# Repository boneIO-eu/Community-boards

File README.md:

# BoneIO Community Boards

This repository contains boards made by boneIO community members. Everybody can share their work, which allows your work to be tested by community!

Requirements:

- Each board need to be in separate directory.
- In directory you need to create files:
  - AUTHORS.md which template you can copy from main directory. It has to constist authors of the board.
  - README.md - description of the board, what is purpose of the board, what it can do, how to connect it etc. 3D visualisation in the file is very welcome.

You want to create board for community!
This is the right place!

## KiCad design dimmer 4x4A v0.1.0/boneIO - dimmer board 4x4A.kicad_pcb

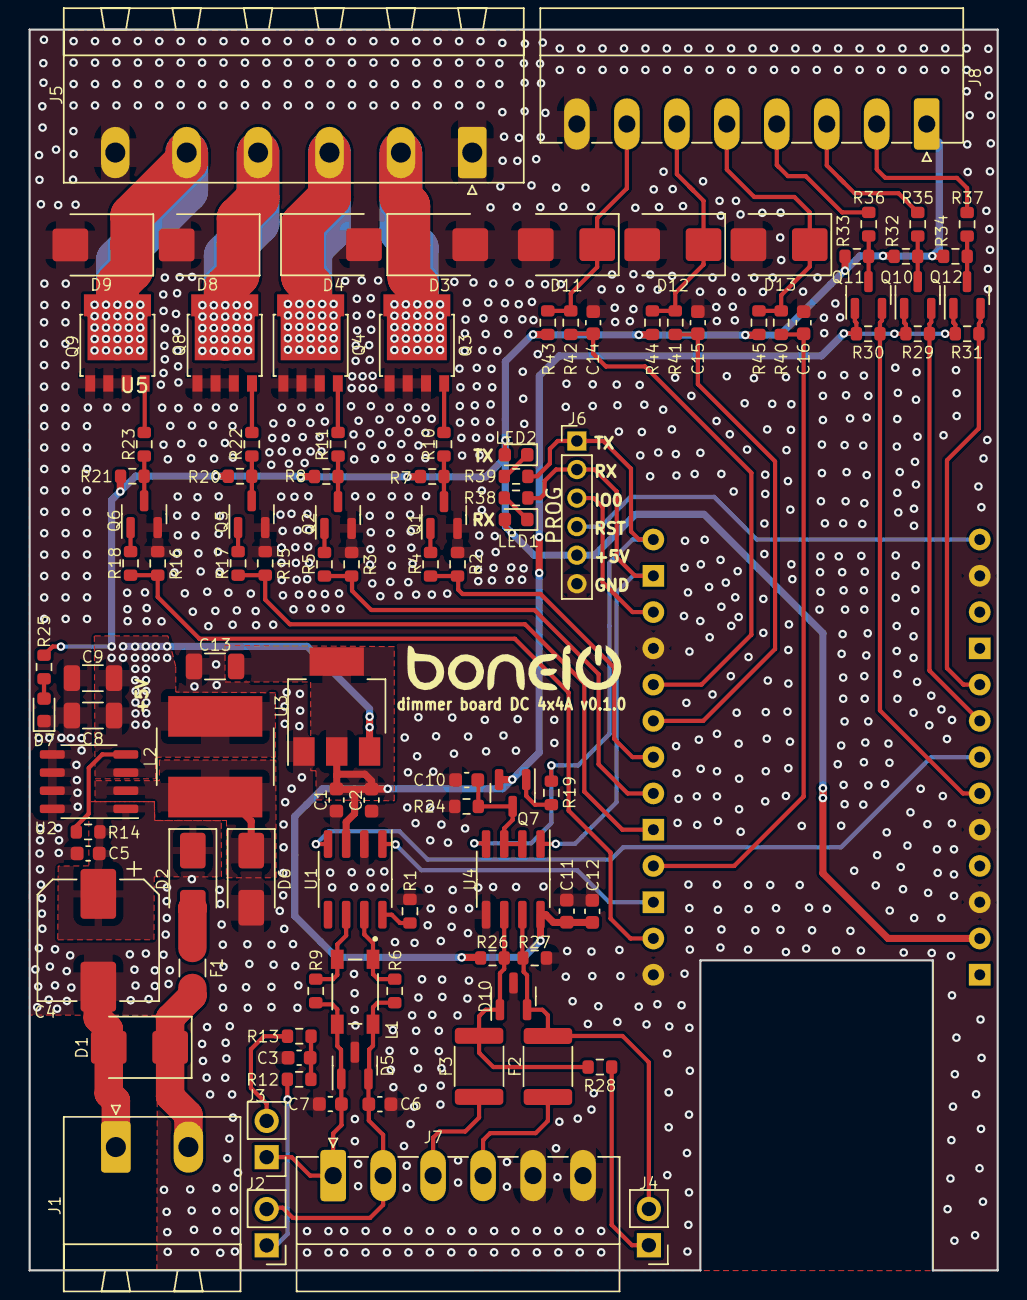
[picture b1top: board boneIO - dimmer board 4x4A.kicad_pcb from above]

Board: 2 copper layers, 67.8 x 86.9 mm, 106 parts (0 on the bottom side), 67 nets.

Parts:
C1, C11: 10uF/C0805; C_0603_1608Metric
C2, C12, C14, C15, C16: 100nF/C0603; C_0603_1608Metric
C3: 4.7nF/C0603; C_0603_1608Metric
C4: 100uF/50V; CP_Elec_8x10
C5, C10: 100n; C_0603_1608Metric
C6, C7: 47pF/C0603; C_0603_1608Metric
C8, C9, C13: 10uF; C_1206_3216Metric
D1, D3, D4, D8, D9: SMBJ28CA; D_SMB
D2, D6: SS34; D_SMA
D5: PESD1CAN; SOT-23
D7: LED_RED; LED_0603_1608Metric
D10: SM712_SOT23; SOT-23
D11, D12, D13: P6SMB6.8A; D_SMB
F1: BSMD1206-100-24V; Fuse_1206_3216Metric
F2, F3: JK-mSMD010-60; Fuse_1812_4532Metric
J1: Screw_Terminal_01x02; PhoenixContact_MSTBA_2,5_2-G-5,08_1x02_P5.08mm_Horizontal
J2, J3: Jumper 60.4R; PinHeader_1x02_P2.54mm_Vertical
J4: Jumper 120R; PinHeader_1x02_P2.54mm_Vertical
J5: RGBW; PhoenixContact_MSTBA_2,5_6-G_1x06_P5.00mm_Horizontal
J6: PROG; PinHeader_1x06_P2.00mm_Vertical
J7: CAN&RS; PhoenixContact_MC_1,5_6-G-3.5_1x06_P3.50mm_Horizontal
J8: Screw_Terminal_01x08; PhoenixContact_MC_1,5_8-G-3.5_1x08_P3.50mm_Horizontal
L1: ACT45B-510; FIL_ACT45B-510-2P-TL003
L2: 68uH; L_Bourns_SRN8040TA
LED1, LED2: LED_BLUE/L0603; LED_0603_1608Metric
Q1, Q2, Q5, Q6: BC817; SOT-23
Q3, Q4, Q8, Q9: PSMN1R2-30YLC; LFPAK56
Q7: BC807; SOT-23
Q10, Q11, Q12: BSS138; SOT-23
R1, R2, R3, R7, R8, R15, R16, R20, R21, R29, R30, R31, R32, R33, R34, R43, R44, R45: 10k/R0603; R_0603_1608Metric
R4, R5, R10, R11, R17, R18, R22, R23: 4.7k/R0603; R_0603_1608Metric
R6, R9: 0k/R0603; R_0603_1608Metric
R12: 60.4k/R0603; R_0603_1608Metric
R13: 60.4R/R0603; R_0603_1608Metric
R14: 100k; R_0603_1608Metric
R19, R24, R26, R27: 4.7k; R_0603_1608Metric
R25, R38, R39: 1.2k/R0603; R_0603_1608Metric
R28: 120R; R_0603_1608Metric
R35, R36, R37: 330R/R0603; R_0603_1608Metric
R40, R41, R42: 330R; R_0603_1608Metric
U1: SN65HVD230; SOIC-8_3.9x4.9mm_P1.27mm
U2: 5V; SO-8_3.9x4.9mm_P1.27mm
U3: AMS1117-3.3; SOT-223-3_TabPin2
U4: MAX485E; SOIC-8_3.9x4.9mm_P1.27mm
U5: WT32-ETH01; WT32-ETH

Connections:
+3V3: C1.2, C2.2, C11.2, C12.2, C13.1, Q7.2 (E), Q10.1 (G), Q11.1 (G), Q12.1 (G), R26.1, R29.1, R30.1, R31.1, U1.3 (VCC), U3.2 (VO), U4.8 (VCC)
+5V: C8.1, C9.1, J6.5, J8.1, L2.2, LED1.2 (A), LED2.2 (A), R7.1, R8.1, R20.1, R21.1, R25.1, R32.1, R33.1, R34.1, R43.1, R44.2, R45.2, U2.3 (FB), U3.3 (VI), U5.25 (5V)
+24V: C4.1, C5.1, D2.1 (K), R14.1, U2.1 (VIN)
A+_OUT: F3.2, J7.3
B-_OUT: F2.2, J7.4
BLUE_OUT: D8.1 (A1), J5.4, Q8.5 (D)
CAN_H: C6.2, D5.2, J2.2, J7.2, L1.4, R6.1
CAN_L: C7.1, D5.1, J3.1, J7.1, L1.3, R9.2
ESP_EN: J6.4, U5.14 (EN)
GND: C1.1, C2.1, C3.2, C4.2, C5.2, C6.1, C7.2, C8.2, C9.2, C10.2, C11.1, C12.1, C13.2, C14.2, C15.2, C16.2, D1.2 (A2), D3.2 (A2), D4.2 (A2), D5.3, D6.2 (A), D7.1 (K), D8.2 (A2), D9.2 (A2), D10.3 (common), D11.2 (A), D12.2 (A), D13.2 (A), J1.1, J5.1, J5.6, J6.6, J7.5, J7.6, J8.8, Q1.2 (E), Q2.2 (E), Q3.1 (S), Q3.2 (S), Q3.3 (S), Q4.1 (S), Q4.2 (S), Q4.3 (S), Q5.2 (E), Q6.2 (E), Q8.1 (S), Q8.2 (S), Q8.3 (S), Q9.1 (S), Q9.2 (S), Q9.3 (S), R1.2, R2.2, R3.2, R15.2, R16.2, R24.2, R27.2, U1.2 (GND), U2.5 (GND), U2.6 (GND), U2.7 (GND), U2.8 (GND), U3.1 (GND), U4.5 (GND), U5.4 (GND), U5.13 (GND), U5.15 (GND), U5.22 (GND), U5.24 (GND)
GPIO0: J6.3, U5.3 (IO0)
GREEN_OUT: D4.1 (A1), J5.3, Q4.5 (D)
INPUT_1: C14.1, R42.1, U5.5 (IO39)
INPUT_2: C15.1, R41.1, U5.6 (IO36)
INPUT_3: C16.1, R40.1, U5.10 (IO35)
unnamed: C3.1, R12.1, R13.2
unnamed: D2.2 (A), F1.1
unnamed: D6.1 (K), L2.1, U2.2 (OUT)
unnamed: D7.2 (A), R25.2
unnamed: D10.1 (A1), F3.1, R26.2, R28.2, U4.6 (A)
unnamed: D10.2 (A2), F2.1, J4.2, R27.1, U4.7 (B)
unnamed: D11.1 (K), J8.7, R42.2, R43.2
unnamed: D12.1 (K), J8.6, R41.2, R44.1
unnamed: D13.1 (K), J8.5, R40.2, R45.1
unnamed: J2.1, R12.2
unnamed: J3.2, R13.1
unnamed: J4.1, R28.1
unnamed: LED1.1 (K), R38.2
unnamed: LED2.1 (K), R39.2
unnamed: Q1.1 (B), R4.1
unnamed: Q1.3 (C), R7.2, R10.2
unnamed: Q2.1 (B), R5.1
unnamed: Q2.3 (C), R8.2, R11.2
unnamed: Q3.4 (G), R10.1
unnamed: Q4.4 (G), R11.1
unnamed: Q5.1 (B), R17.1
unnamed: Q5.3 (C), R20.2, R22.2
unnamed: Q6.1 (B), R18.1
unnamed: Q6.3 (C), R21.2, R23.2
unnamed: Q7.1 (B), R19.1
unnamed: C10.1, Q7.3 (C), R24.1, U4.2 (~RE), U4.3 (DE)
unnamed: Q8.4 (G), R22.1
unnamed: Q9.4 (G), R23.1
unnamed: Q10.3 (D), R32.2, R35.2
unnamed: Q11.3 (D), R33.2, R36.2
unnamed: Q12.3 (D), R34.2, R37.2
unnamed: L1.1, R6.2, U1.7 (CANH)
unnamed: L1.2, R9.1, U1.6 (CANL)
unnamed: R1.1, U1.8 (Rs)
unnamed: R14.2, U2.4 (ON/OFF)
OUT_1: R2.1, R4.2, U5.7 (IO15)
OUT_2: R3.1, R5.2, U5.8 (IO14)
OUT_3: R15.1, R17.2, U5.9 (IO12)
OUT_4: R16.1, R18.2, U5.12 (IO2)
RED_OUT: D3.1 (A1), J5.2, Q3.5 (D)
RX: J6.2, R38.1, U4.1 (RO), U5.2 (RXD)
RX_CAN: U1.4 (R), U5.20 (IO5)
TX: J6.1, R19.2, R39.1, U4.4 (DI), U5.1 (TXD)
TX_CAN: U1.1 (D), U5.11 (IO4)
VDD: D1.1 (A1), F1.2, J1.2
WHITE_OUT: D9.1 (A1), J5.5, Q9.5 (D)
WS281x1: Q12.2 (S), R31.2, U5.18 (IO32)
WS281x1_OUT: J8.2, R37.1
WS281x2: Q10.2 (S), R29.2, U5.19 (IO33)
WS281x2_OUT: J8.3, R35.1
WS281x3: Q11.2 (S), R30.2, U5.21 (IO17)
WS281x3_OUT: J8.4, R36.1

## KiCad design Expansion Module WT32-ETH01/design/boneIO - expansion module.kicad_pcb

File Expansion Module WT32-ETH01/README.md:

# boneIO module expander WT32-ETH01

This software script allows you to use the ESP32 + RS485 transceiver to interact with relay boards to boneIO.

It provides all known information via MQTT.

This allows you to integrate the device with Home Assistant.

You can find the configuration YAML files in the `yaml` folder.

## Foto

## Pinout
1. 
Power input
24 DC power supply

2.
RS485
TX 				- GPIO1
RX 				- GPIO3
Flow Control  	- GPIO4

3. 
USB
USB-C is for uploading software

4.
WT32-ETH01
ESP32 controller right with Ethernet for MQTT communication

5.
INPUTS
Digital inputs controlled by low state
IN1 - GPIO39
IN2 - GPIO36
IN3 - GPIO15
IN4 - GPIO14
IN5 - GPIO35
IN6 - GPIO17

6.
I2C
SDA - GPIO32
SCL - GPIO33
Frequency - 100kHz

7.
1-WIRE
DATA - GPIO5

Exit and input description:

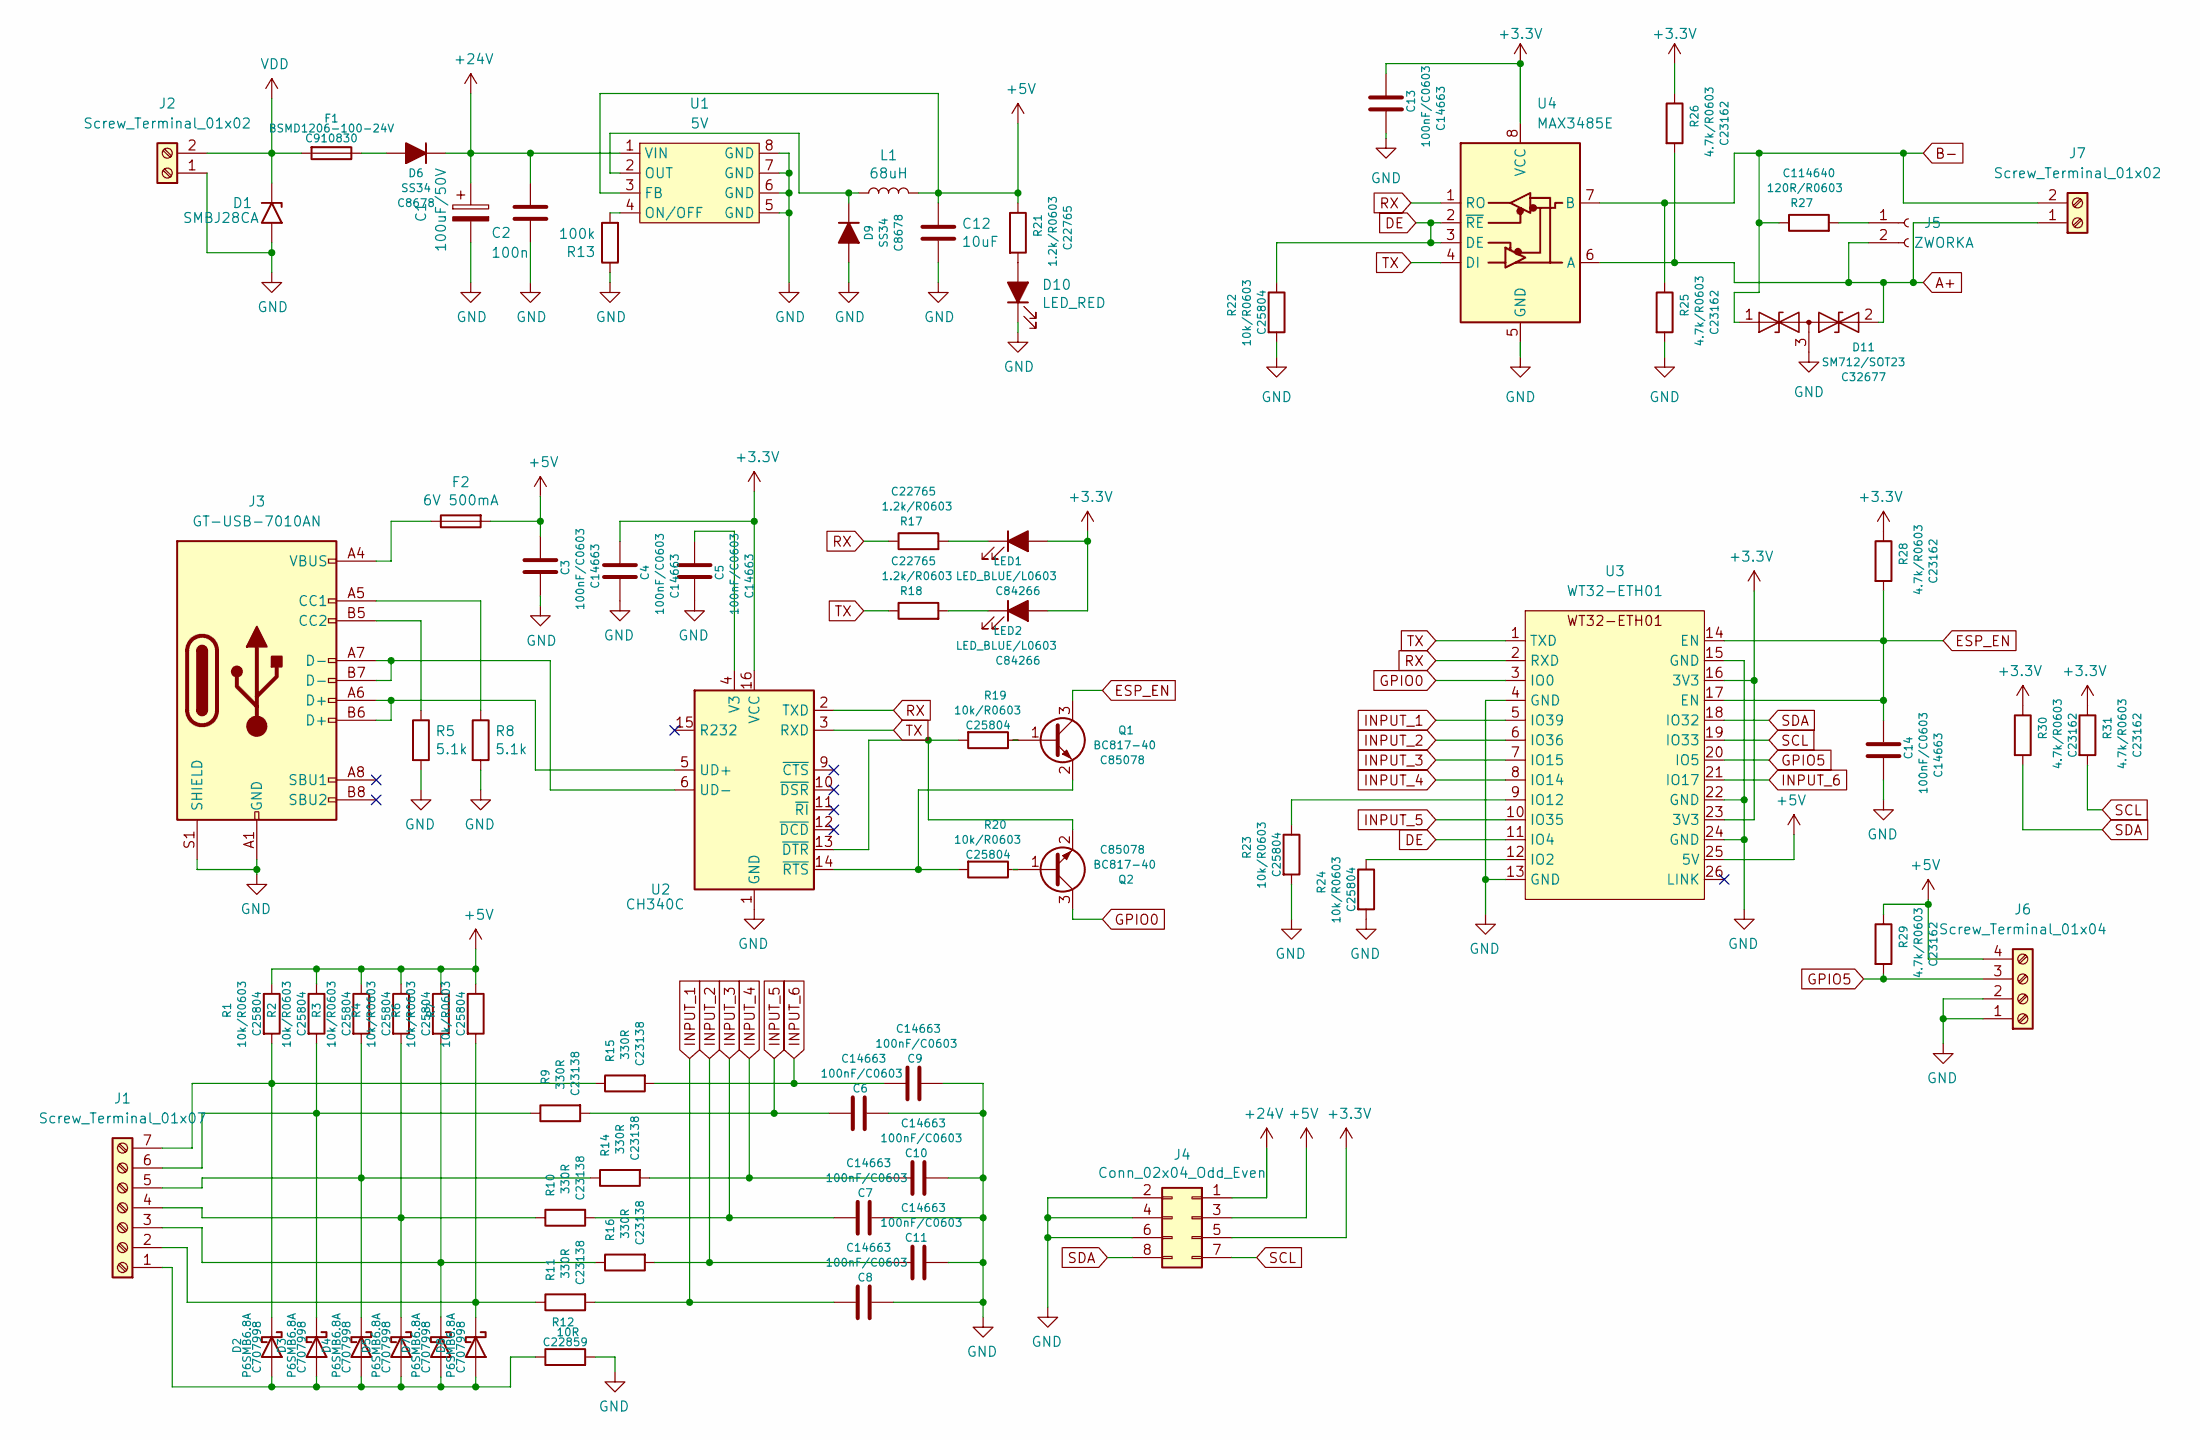
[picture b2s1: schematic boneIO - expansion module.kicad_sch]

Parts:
C1: 100uF/50V; CP_Elec_8x10; JLCPCB C72480
C2: 100n; C_0603_1608Metric; JLCPCB C14663
C3, C4, C5, C6, C7, C8, C9, C10, C11, C13, C14: 100nF/C0603; C_0603_1608Metric; JLCPCB C14663
C12: 10uF; C_1206_3216Metric; JLCPCB C107149
D1: SMBJ28CA; D_SMB
D2, D3, D4, D5, D7, D8: P6SMB6.8A; D_SMB; JLCPCB C707998
D6, D9: SS34; D_SMA; JLCPCB C8678
D10: LED_RED; LED_0603_1608Metric; JLCPCB C84256
D11: SM712/SOT23; SOT-23; JLCPCB C32677
F1: BSMD1206-100-24V; Fuse_1206_3216Metric; JLCPCB C910830
F2: 6V 500mA; Fuse_1206_3216Metric
J1: Screw_Terminal_01x07; PhoenixContact_MSTBA_2,5_7-G-5,08_1x07_P5.08mm_Horizontal
J2, J7: Screw_Terminal_01x02; PhoenixContact_MSTBA_2,5_2-G-5,08_1x02_P5.08mm_Horizontal
J3: GT-USB-7010AN; USB_C_Receptacle_HRO_TYPE-C-31-M-12
J4: Conn_02x04_Odd_Even; PinHeader_2x04_P2.54mm_Vertical
J5: ZWORKA; PinHeader_1x02_P2.54mm_Vertical
J6: Screw_Terminal_01x04; PhoenixContact_MSTBA_2,5_4-G-5,08_1x04_P5.08mm_Horizontal
L1: 68uH; L_Bourns_SRN8040TA; JLCPCB C338848
LED1, LED2: LED_BLUE/L0603; LED_0603_1608Metric; JLCPCB C84266
Q1, Q2: BC817-40; SOT-23; JLCPCB C85078
R1, R2, R3, R4, R6, R7, R19, R20, R22, R23, R24: 10k/R0603; R_0603_1608Metric; JLCPCB C25804
R5, R8: 5.1k; R_0603_1608Metric
R9, R10, R11, R14, R15, R16: 330R; R_0603_1608Metric; JLCPCB C23138
R12: 10R; R_0603_1608Metric; JLCPCB C22859
R13: 100k; R_0603_1608Metric; JLCPCB C269704
R17, R18, R21: 1.2k/R0603; R_0603_1608Metric; JLCPCB C22765
R25, R26, R28, R29, R30, R31: 4.7k/R0603; R_0603_1608Metric; JLCPCB C23162
R27: 120R/R0603; R_0603_1608Metric; JLCPCB C114640
U1: 5V; SO-8_3.9x4.9mm_P1.27mm
U2: CH340C; SOIC-16_3.9x9.9mm_P1.27mm
U3: WT32-ETH01; WT32_ETH01
U4: MAX3485E; SOP-8_3.9x4.9mm_P1.27mm; JLCPCB C9943

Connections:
+3V3: C4.1, C13.1, J4.5, LED1.2 (A), LED2.2 (A), R26.1, R28.1, R30.1, R31.1, U2.16 (VCC), U3.16 (3V3), U3.23 (3V3), U4.8 (VCC)
+5V: C3.1, C12.1, F2.2, J4.3, J6.4, L1.2, R1.1, R2.1, R3.1, R4.1, R6.1, R7.1, R21.1, R29.1, U1.3 (FB), U3.25 (5V)
+24V: C1.1, C2.1, D6.1 (K), J4.1, U1.1 (VIN)
A+: D11.2 (A2), J5.2, J7.1, R26.2, U4.6 (A)
B-: D11.1 (A1), J7.2, R25.1, R27.1, U4.7 (B)
DE: R22.1, U3.11 (IO4), U4.2 (~RE), U4.3 (DE)
ESP_EN: C14.1, Q1.3 (C), R28.2, U3.14 (EN), U3.17 (EN)
GND: C1.2, C2.2, C3.2, C4.2, C5.2, C6.2, C7.2, C8.2, C9.2, C10.2, C11.2, C12.2, C13.2, C14.2, D1.2 (A2), D9.2 (A), D10.1 (K), D11.3 (common), J2.1, J3.A1 (GND), J3.A12 (GND), J3.B1 (GND), J3.B12 (GND), J3.S1 (SHIELD), J4.2, J4.4, J4.6, J6.1, J6.2, R5.2, R8.2, R12.2, R13.1, R22.2, R23.2, R24.2, R25.2, U1.5 (GND), U1.6 (GND), U1.7 (GND), U1.8 (GND), U2.1 (GND), U3.4 (GND), U3.13 (GND), U3.15 (GND), U3.22 (GND), U3.24 (GND), U4.5 (GND)
GPIO0: Q2.3 (C), U3.3 (IO0)
GPIO5: J6.3, R29.2, U3.20 (IO5)
INPUT_1: C8.1, R11.2, U3.5 (IO39)
INPUT_2: C11.1, R16.2, U3.6 (IO36)
INPUT_3: C7.1, R10.2, U3.7 (IO15)
INPUT_4: C10.1, R14.2, U3.8 (IO14)
INPUT_5: C6.1, R9.2, U3.10 (IO35)
INPUT_6: C9.1, R15.2, U3.21 (IO17)
unnamed: C5.1, U2.4 (V3)
unnamed: D2.1 (K), J1.7, R1.2, R15.1
unnamed: D2.2 (A), D3.2 (A), D4.2 (A), D5.2 (A), D7.2 (A), D8.2 (A), J1.1, R12.1
unnamed: D3.1 (K), J1.6, R2.2, R9.1
unnamed: D4.1 (K), J1.5, R3.2, R14.1
unnamed: D5.1 (K), J1.4, R4.2, R10.1
unnamed: D6.2 (A), F1.1
unnamed: D7.1 (K), J1.3, R6.2, R16.1
unnamed: D8.1 (K), J1.2, R7.2, R11.1
unnamed: D9.1 (K), L1.1, U1.2 (OUT)
unnamed: D10.2 (A), R21.2
unnamed: F2.1, J3.A4 (VBUS), J3.A9 (VBUS), J3.B4 (VBUS), J3.B9 (VBUS)
unnamed: J3.A5 (CC1), R8.1
unnamed: J3.A6 (D+), J3.B6 (D+), U2.5 (UD+)
unnamed: J3.A7 (D-), J3.B7 (D-), U2.6 (UD-)
unnamed: J3.B5 (CC2), R5.1
unnamed: J5.1, R27.2
unnamed: LED1.1 (K), R17.2
unnamed: LED2.1 (K), R18.2
unnamed: Q1.1 (B), R19.1
unnamed: Q1.2 (E), R20.2, U2.14 (~RTS)
unnamed: Q2.1 (B), R20.1
unnamed: Q2.2 (E), R19.2, U2.13 (~DTR)
unnamed: R13.2, U1.4 (ON/OFF)
unnamed: R23.1, U3.9 (IO12)
unnamed: R24.1, U3.12 (IO2)
RX: R17.1, U2.2 (TXD), U3.2 (RXD), U4.1 (RO)
SCL: J4.7, R31.2, U3.19 (IO33)
SDA: J4.8, R30.2, U3.18 (IO32)
TX: R18.1, U2.3 (RXD), U3.1 (TXD), U4.4 (DI)
VDD: D1.1 (A1), F1.2, J2.2

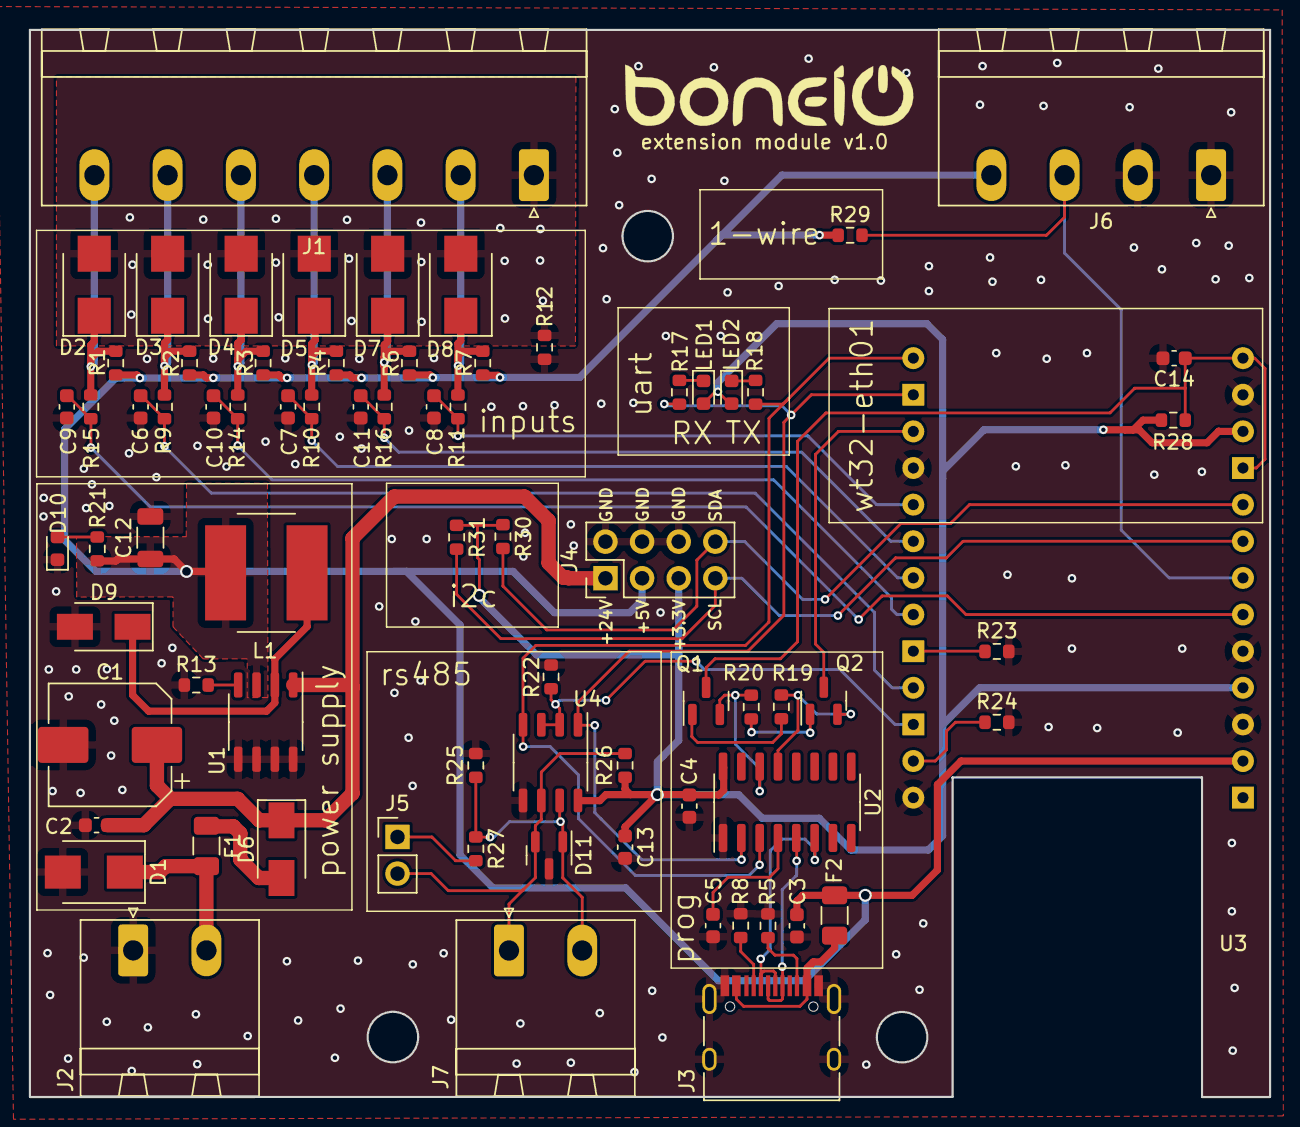
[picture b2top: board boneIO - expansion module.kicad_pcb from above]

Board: 2 copper layers, 86.0 x 74.0 mm, 74 parts (0 on the bottom side), 47 nets.
